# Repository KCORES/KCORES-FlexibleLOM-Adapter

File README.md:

# KCORES-FlexibleLOM-Adapter

KCORES FlexibleLOM to PCIe x8 adapter and baffle model. The FLR series network cards can be used on normal motherboards PCIe slots, including common Gigabit, 10G, and 40G network cards. Due to size limitations, only full-height baffle design is available.  

KCORES FlexibleLOM 转 PCIe x8 转接卡开源设计，可以让普通电脑主板的 PCIe 槽使用 FLR 系列网卡，包括常见的千兆、万兆、40G网卡。由于尺寸限制，只提供全高挡板设计。

- 2 Layers PCB design, Easy to make  
双层PCB设计，容易制造

- Impedance matching by Polar SI9000  
使用 Polar SI9000 计算阻抗

- Size less than 10x10cm  
小尺寸，不超过 10x10cm

**[KCORES 官方网站](http://kcores.com/)**

**HomeLab 交流 QQ 群: 826702309**

# Compatibility

- ✔ Recommend 推荐
- 🟡 Compatible 兼容
- ❌ Fail 不兼容

| FlexibleLOM  | NIC Model               | Connectors        | [v1.0](https://github.com/KCORES/KCORES-FlexibleLOM-Adapter/releases/tag/v1.0) |   v1.1 | SKU | SP | AS | Notes |
| ------------ | ----------------------- | ----------------- | :----: | :----: | ---- | ---- | ---- | ---- |
| 331FLR       | Broadcom BCM5719        | Quad RJ45 GbE     | ❌     | ✔     |            |            |            | 
| 366FLR       | intel i350              | Quad RJ45 GbE     | ✔      | ✔     |            |            |            | 
| 530FLR-SFP+  | Broadcom BCM57810S      | Dual SFP+ 10GbE   | ❌     | ✔     | 647581-B21 | 649869-001 | 647579-001 |
| 533FLR-T     | Broadcom BCM57810S      | Dual RJ45 10GbE   | ✔      | ✔     | 700759-B21 | 701534-001 | 700757-001 |
| 534FLR-SFP+  | Cavium BCM57810S        | Dual SFP+ 10GbE   |        |       |       -B21 |       -001 |       -001 |
| 535FLR-T     | Broadcom BCM57416       | Dual RJ45 10GbE   |        |       |       -B21 |       -001 |       -001 | RoCE V2, 15W |
| 536FLR-T     | QLogic  57840S          | Quad RJ45 10GbE   |        |       |       -B21 |       -001 |       -001 | 9W |
| 537FLR-SFP+  | Broadcom BCM57412       | Dual SFP+ 10GbE   |        |       |       -B21 |       -001 |       -001 | iWARP, 14W |
| ConnectX3ALOM| Mellanox ConnectX-3     | Single SFP+ 10GbE |        | ✔     | 682148-B21 | 682625-001 | 682150-001 | 
| 544FLR-QSFP  | Mellanox ConnectX-3     | Dual QSFP+ 40GbE  |        |       | 649282-B21 | 656090-001 | 661686-001 |
| 544FLR-QSFP  | Mellanox ConnectX-3     | Dual QSFP+ 40GbE  | ✔      | ✔     | 649283-B21 | 656091-001 | 661687-001 |
| 544+FLR-SFP+ | Mellanox ConnectX-3 Pro | Single SFP+ 10GbE | ✔      | ✔     | 724206-B21 | 731850-001 | 724210-001 | 
| 544+FLR-QSFP | Mellanox ConnectX-3 Pro | Dual QSFP+ 40GbE  | ✔      | ✔     | 764285-B21 | 764737-001 | 764618-001 |
| 545FLR-QSFP  | Mellanox Connect-IB     | Dual QSFP+ 56G IB |        |       | 7     -B21 | 7     -001 | 7     -001 |
| 546+FLR-SFP+ | Mellanox ConnectX-3 Pro | Dual SFP+ 10GbE   |        |       | 779799-B21 | 7     -001 | 7     -001 |
| 547+FLR-QSFP | Mellanox ConnectX-5     | Dual QSFP+ 40GbE  |        |       | 879482-B21 | 8     -001 | 8     -001 |
| 554FLR-SFP+  | Emulex BE3 684213-B21   | Dual SFP+ 10GbE   |        |       | 629142-B21 | 634026-001 | 629140-001 |
| 556FLR-T     | Emulex XE-104           | Dual RJ45 10GbE   |        |       | 794525-B21 |            |            | RoCE V1 |
| 556FLR-SFP+  | Emulex XE-102 727060-B21 | Dual SFP+ 10GbE   |        |       | 732456-B21 | 764460-001 | 732454-001 | RoCE V1 |
| 560FLR-SFP+  | intel 82599             | Dual SFP+ 10GbE   | ✔      | ✔     |            |            |            | 
| 561FLR-T     | intel X540              | Dual RJ45 10GbE   | ✔      | ✔     | 700699-B21 | 701525-001 | 700697-001 |
| 562FLR-T     | intel X550              | Dual RJ45 10GbE   | ✔      | ✔     | 817745-B21 | 840138-001 | 817743 -001|
| 562FLR-SFP+  | intel X710              | Dual SFP+ 10GbE   |        |       | 727054-B21 | 7     -001 | 7     -001 |
| 570FLR-SFP+  | SFC 9020                | Dual      10GbE   | ✔      | ✔     | 717491-B21 | 717710-001 | 717489-001 | 

- **Note:**  
Some models of 544FLR-QSFP only support 10GbE and QDR. Please check
 the **Part Number** before buying!  
544FLR-QSFP 部分型号只支持 10GbE 和 QDR，请在购买前检查**物料号**！

# Directory

- /Documents/    
说明文档

- /Electricals/  
PCB design files  
3D 模型和挡板设计文件

- /Firmwares/  
Firmwares guide  
固件刷写相关教程

- /Mechanicals/  
FlexibleLOM Model and PCI Baffle  
FLR 卡模型及 PCI 挡板设计文件

# Photos & Renderings

# Thanks To

- [@Wangrb (Original Adapter Card Design)](https://github.com/Wangrb)
- [@AlphaArea (Main Contributer)](https://github.com/alphaarea)
- [@MistyMoonR (3D Model)](https://github.com/MistyMoonR)  
- [@Karminski (Photo)](https://github.com/karminski)

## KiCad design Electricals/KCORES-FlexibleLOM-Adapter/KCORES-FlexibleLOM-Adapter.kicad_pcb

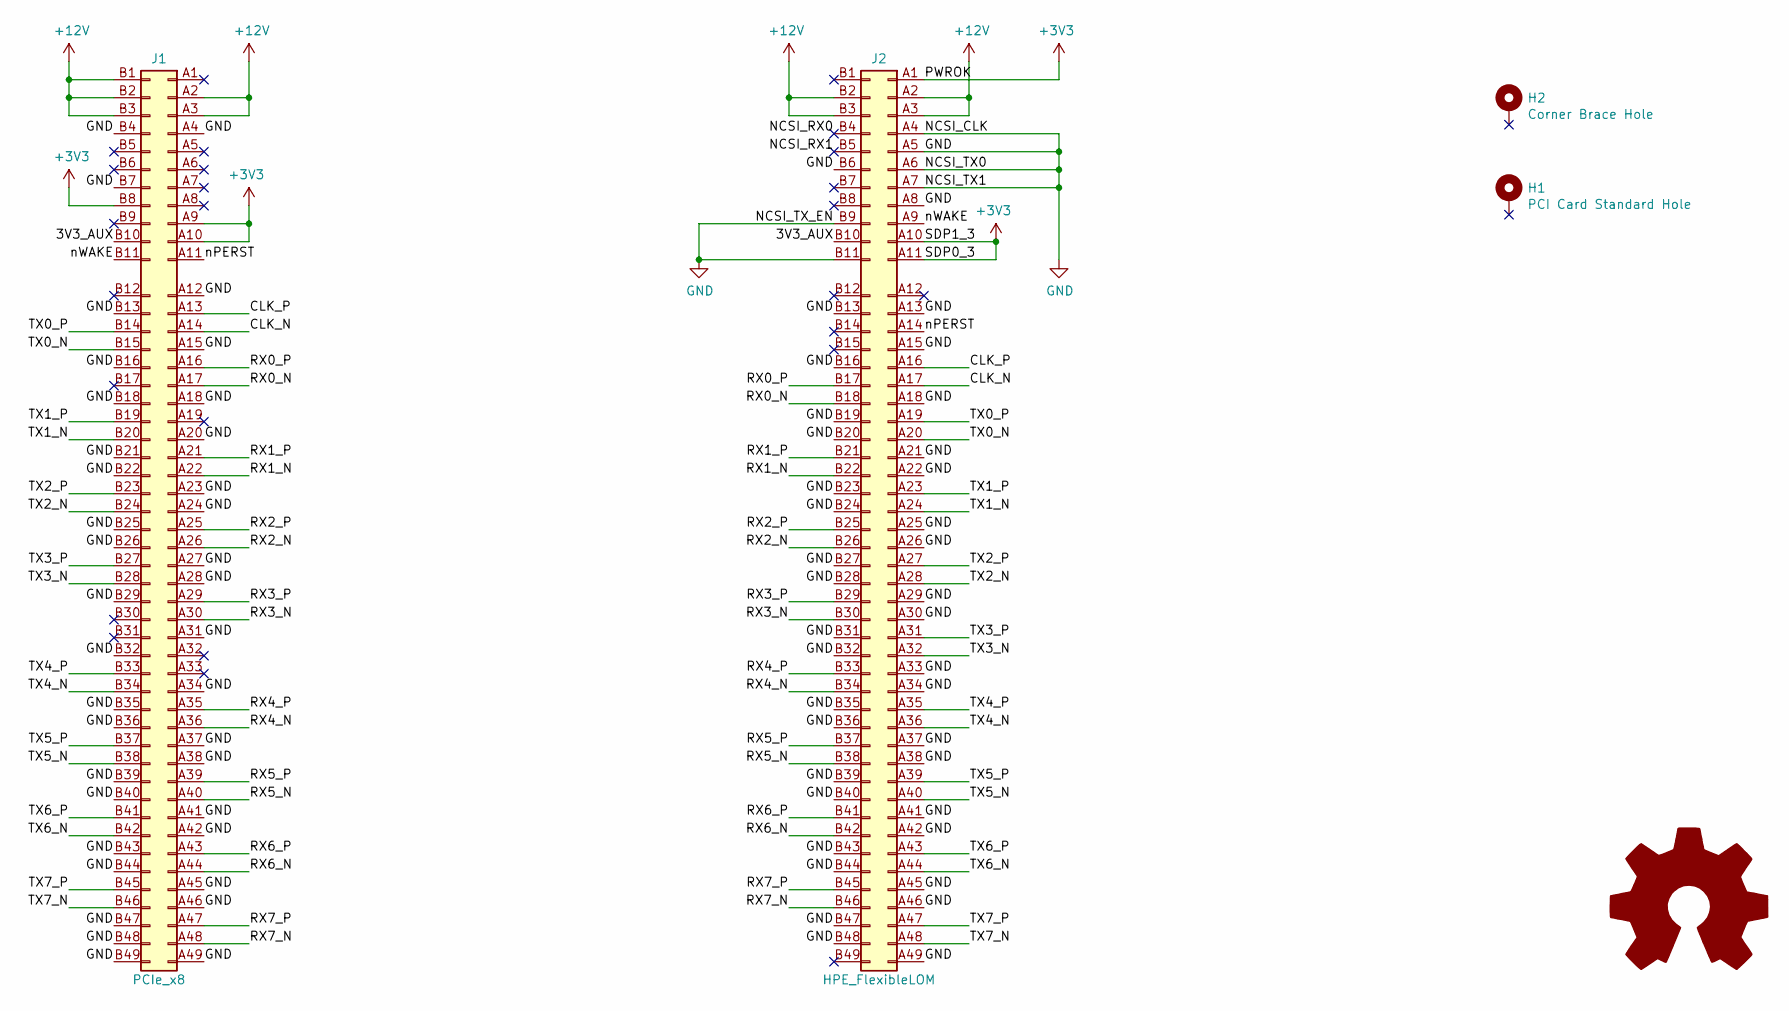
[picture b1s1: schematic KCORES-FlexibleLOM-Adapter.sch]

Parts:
H1: PCI Card Standard Hole; MountingHole_3.2mm_M3_Pad
H2: Corner Brace Hole; MountingHole_3.2mm_M3_Pad
J1: PCIe_x8; BUS_PCIexpress_x8
J2: HPE_FlexibleLOM; BUS_PCIexpress_x8_Straddle_Mount_Modify
LOGO1: Logo_Open_Hardware_Large; OSHW-Logo2_14.6x12mm_SilkScreen

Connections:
+3V3: J1.A9, J1.A10, J1.B8, J2.A1, J2.A10, J2.A11
+12V: J1.A2, J1.A3, J1.B1, J1.B2, J1.B3, J2.A2, J2.A3, J2.B2, J2.B3
/3V3_AUX: J1.B10, J2.B10
/CLK_N: J1.A14, J2.A17
/CLK_P: J1.A13, J2.A16
/NCSI_RX0: J2.B4
/NCSI_RX1: J2.B5
/RX0_N: J1.A17, J2.B18
/RX0_P: J1.A16, J2.B17
/RX1_N: J1.A22, J2.B22
/RX1_P: J1.A21, J2.B21
/RX2_N: J1.A26, J2.B26
/RX2_P: J1.A25, J2.B25
/RX3_N: J1.A30, J2.B30
/RX3_P: J1.A29, J2.B29
/RX4_N: J1.A36, J2.B34
/RX4_P: J1.A35, J2.B33
/RX5_N: J1.A40, J2.B38
/RX5_P: J1.A39, J2.B37
/RX6_N: J1.A44, J2.B42
/RX6_P: J1.A43, J2.B41
/RX7_N: J1.A48, J2.B46
/RX7_P: J1.A47, J2.B45
/TX0_N: J1.B15, J2.A20
/TX0_P: J1.B14, J2.A19
/TX1_N: J1.B20, J2.A24
/TX1_P: J1.B19, J2.A23
/TX2_N: J1.B24, J2.A28
/TX2_P: J1.B23, J2.A27
/TX3_N: J1.B28, J2.A32
/TX3_P: J1.B27, J2.A31
/TX4_N: J1.B34, J2.A36
/TX4_P: J1.B33, J2.A35
/TX5_N: J1.B38, J2.A40
/TX5_P: J1.B37, J2.A39
/TX6_N: J1.B42, J2.A44
/TX6_P: J1.B41, J2.A43
/TX7_N: J1.B46, J2.A48
/TX7_P: J1.B45, J2.A47
/nPERST: J1.A11, J2.A14
/nWAKE: J1.B11, J2.A9
GND: J1.A4, J1.A12, J1.A15, J1.A18, J1.A20, J1.A23, J1.A24, J1.A27, J1.A28, J1.A31, J1.A34, J1.A37, J1.A38, J1.A41, J1.A42, J1.A45, J1.A46, J1.A49, J1.B4, J1.B7, J1.B13, J1.B16, J1.B18, J1.B21, J1.B22, J1.B25, J1.B26, J1.B29, J1.B32, J1.B35, J1.B36, J1.B39, J1.B40, J1.B43, J1.B44, J1.B47, J1.B48, J1.B49, J2.A4, J2.A5, J2.A6, J2.A7, J2.A8, J2.A13, J2.A15, J2.A18, J2.A21, J2.A22, J2.A25, J2.A26, J2.A29, J2.A30, J2.A33, J2.A34, J2.A37, J2.A38, J2.A41, J2.A42, J2.A45, J2.A46, J2.A49, J2.B6, J2.B9, J2.B11, J2.B13, J2.B16, J2.B19, J2.B20, J2.B23, J2.B24, J2.B27, J2.B28, J2.B31, J2.B32, J2.B35, J2.B36, J2.B39, J2.B40, J2.B43, J2.B44, J2.B47, J2.B48

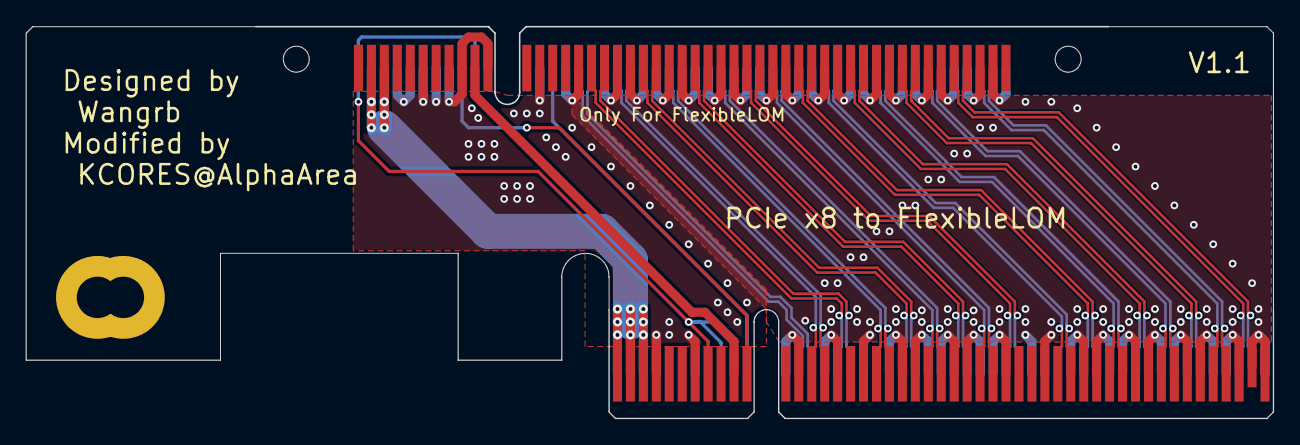
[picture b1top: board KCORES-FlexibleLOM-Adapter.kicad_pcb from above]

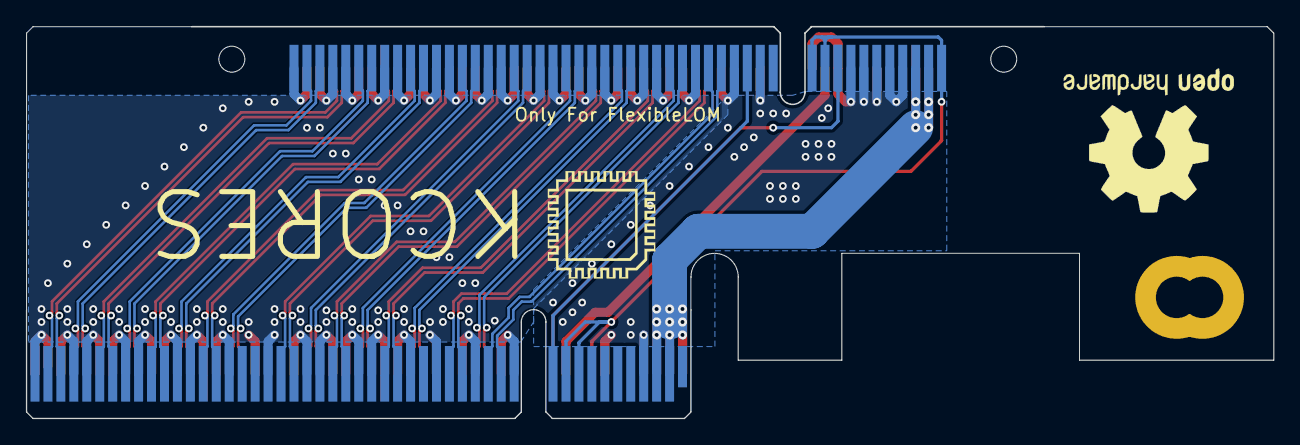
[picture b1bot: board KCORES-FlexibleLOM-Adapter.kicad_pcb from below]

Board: 2 copper layers, 96.3 x 30.2 mm, 5 parts (2 on the bottom side), 40 nets.

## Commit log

2020-10-05 readme
2020-10-05 Create add
2020-10-05 ADD Photo.
2020-10-06 model readme
2020-10-06 fix thanks
2020-10-06 fix gif
2020-10-10 upload KiCAD project
2020-10-24 new PCI Baffle
2020-10-29 add img
2020-10-29 fix readme
2020-10-29 add step
2020-10-29 fix readme 2
2020-11-13 Create V1 Branch
2020-11-14 V1.0 Release
2020-11-14 V1.0 Fix
2020-11-14 v1.1
2021-10-11 Create .gitattributes
    这个文件能使GitHub正确的把KiCAD文件识别到语言统计中，并显示repo使用的语言。效果见图
    ![image](https://user-images.githubusercontent.com/75297777/133580531-d0625566-f7d3-4a87-b6a8-3b0e281ab43e.png)
2021-10-11 微调，适应淘宝量产挡板
    1. 微调了转接座到挡板的距离
    2. 调整了金手指处的阻焊开窗，便于倒角加工
    3. 微调了铺铜规则，从1mil调整到3mm，以减小干扰
    4. 调整了pcie的B3引脚的走线，B3引脚原本接入+12V，现改为悬空
    以上改动均另存为了一个新文件夹，不影响原文件
2022-02-14 add: more adapters and part number
2022-02-14 mod: update pn
2022-02-16 update: cx3 alom pn
2022-02-24 update: new info
2022-12-01 Update README.md
    update support list: add 562FLR-T
